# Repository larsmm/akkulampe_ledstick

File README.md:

# Replacement LED Board for Flashlight

This project provides a high-quality replacement LED board for a flashlight that can be found on for example aliexpress:
- [https://de.aliexpress.com/item/1005009771645768.html](https://de.aliexpress.com/item/1005009771645768.html)
- [https://de.aliexpress.com/item/1005009476677225.html](https://de.aliexpress.com/item/1005009476677225.html)

Flashlight features:
- Switching converters for 5 W charging
- Flicker-free dimming
- No distracting flashing modes
- Slots for two 18650 lithium-ion batteries

The flashlight uses two types of LEDs: an 8 cm LED stick and two LEDs at the top.

This board replaces the LED stick to allow the use of higher-quality LEDs.
After researching suitable options, I found **Bridgelux Thrive** LEDs to deliver some of the best white-light quality available.
A versatile, pleasant color temperature for general use is 3500 K.

## LED Specifications
- **Type:** Bridgelux Thrive BXEN-35S-11M-3C [Datasheet](https://www.bridgelux.com/sites/default/files/resource_media/DS312%20SMD%202835%20Thrive97%200.5W%203V%20150mA%20BXEN-XXS-11M-3C%20Rev%20C%2020220802.pdf)
- **Overview:** [https://www.bridgelux.com/thrive](https://www.bridgelux.com/thrive)
- 3500 K: CRI > 97, R1-R15 > 93 @ ~100 lm/W

## Ordering
I ordered the boards at JLCPCB including PCB assembly and global sourced parts.

## Project Structure
- kicad: KiCad 9 project
- kicad/production: JLCPCB export made by [Fabrication-Toolkit](https://github.com/bennymeg/Fabrication-Toolkit)

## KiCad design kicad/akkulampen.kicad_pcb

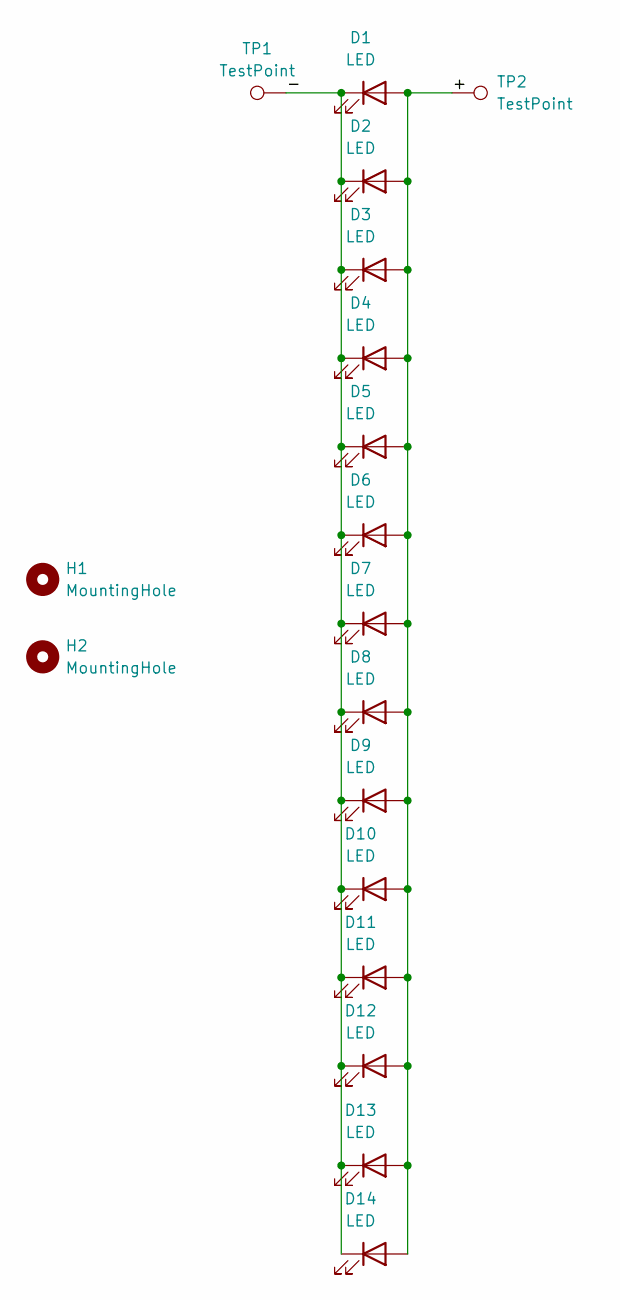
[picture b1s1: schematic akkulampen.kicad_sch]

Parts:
D1, D2, D3, D4, D5, D6, D7, D8, D9, D10, D11, D12, D13, D14: LED; LED_PLCC_2835
H1, H2: MountingHole; MountingHole_2.1mm
TP1, TP2: TestPoint; TestPoint_Keystone_5015_Micro_Mini

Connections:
/+: D1.2 (A), D2.2 (A), D3.2 (A), D4.2 (A), D5.2 (A), D6.2 (A), D7.2 (A), D8.2 (A), D9.2 (A), D10.2 (A), D11.2 (A), D12.2 (A), D13.2 (A), D14.2 (A), TP2.1
/-: D1.1 (K), D2.1 (K), D3.1 (K), D4.1 (K), D5.1 (K), D6.1 (K), D7.1 (K), D8.1 (K), D9.1 (K), D10.1 (K), D11.1 (K), D12.1 (K), D13.1 (K), D14.1 (K), TP1.1

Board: 2 copper layers, 20 parts (0 on the bottom side), 2 nets, no tracks yet.

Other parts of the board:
kibuzzard-68B176D2: G***; kibuzzard-68B176D2
kibuzzard-68B17760: G***; kibuzzard-68B17760

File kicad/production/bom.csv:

Designator,Footprint,Quantity,Value,LCSC Part #
"D1, D10, D11, D12, D13, D14, D2, D3, D4, D5, D6, D7, D8, D9",LED_PLCC_2835,14,LED,
